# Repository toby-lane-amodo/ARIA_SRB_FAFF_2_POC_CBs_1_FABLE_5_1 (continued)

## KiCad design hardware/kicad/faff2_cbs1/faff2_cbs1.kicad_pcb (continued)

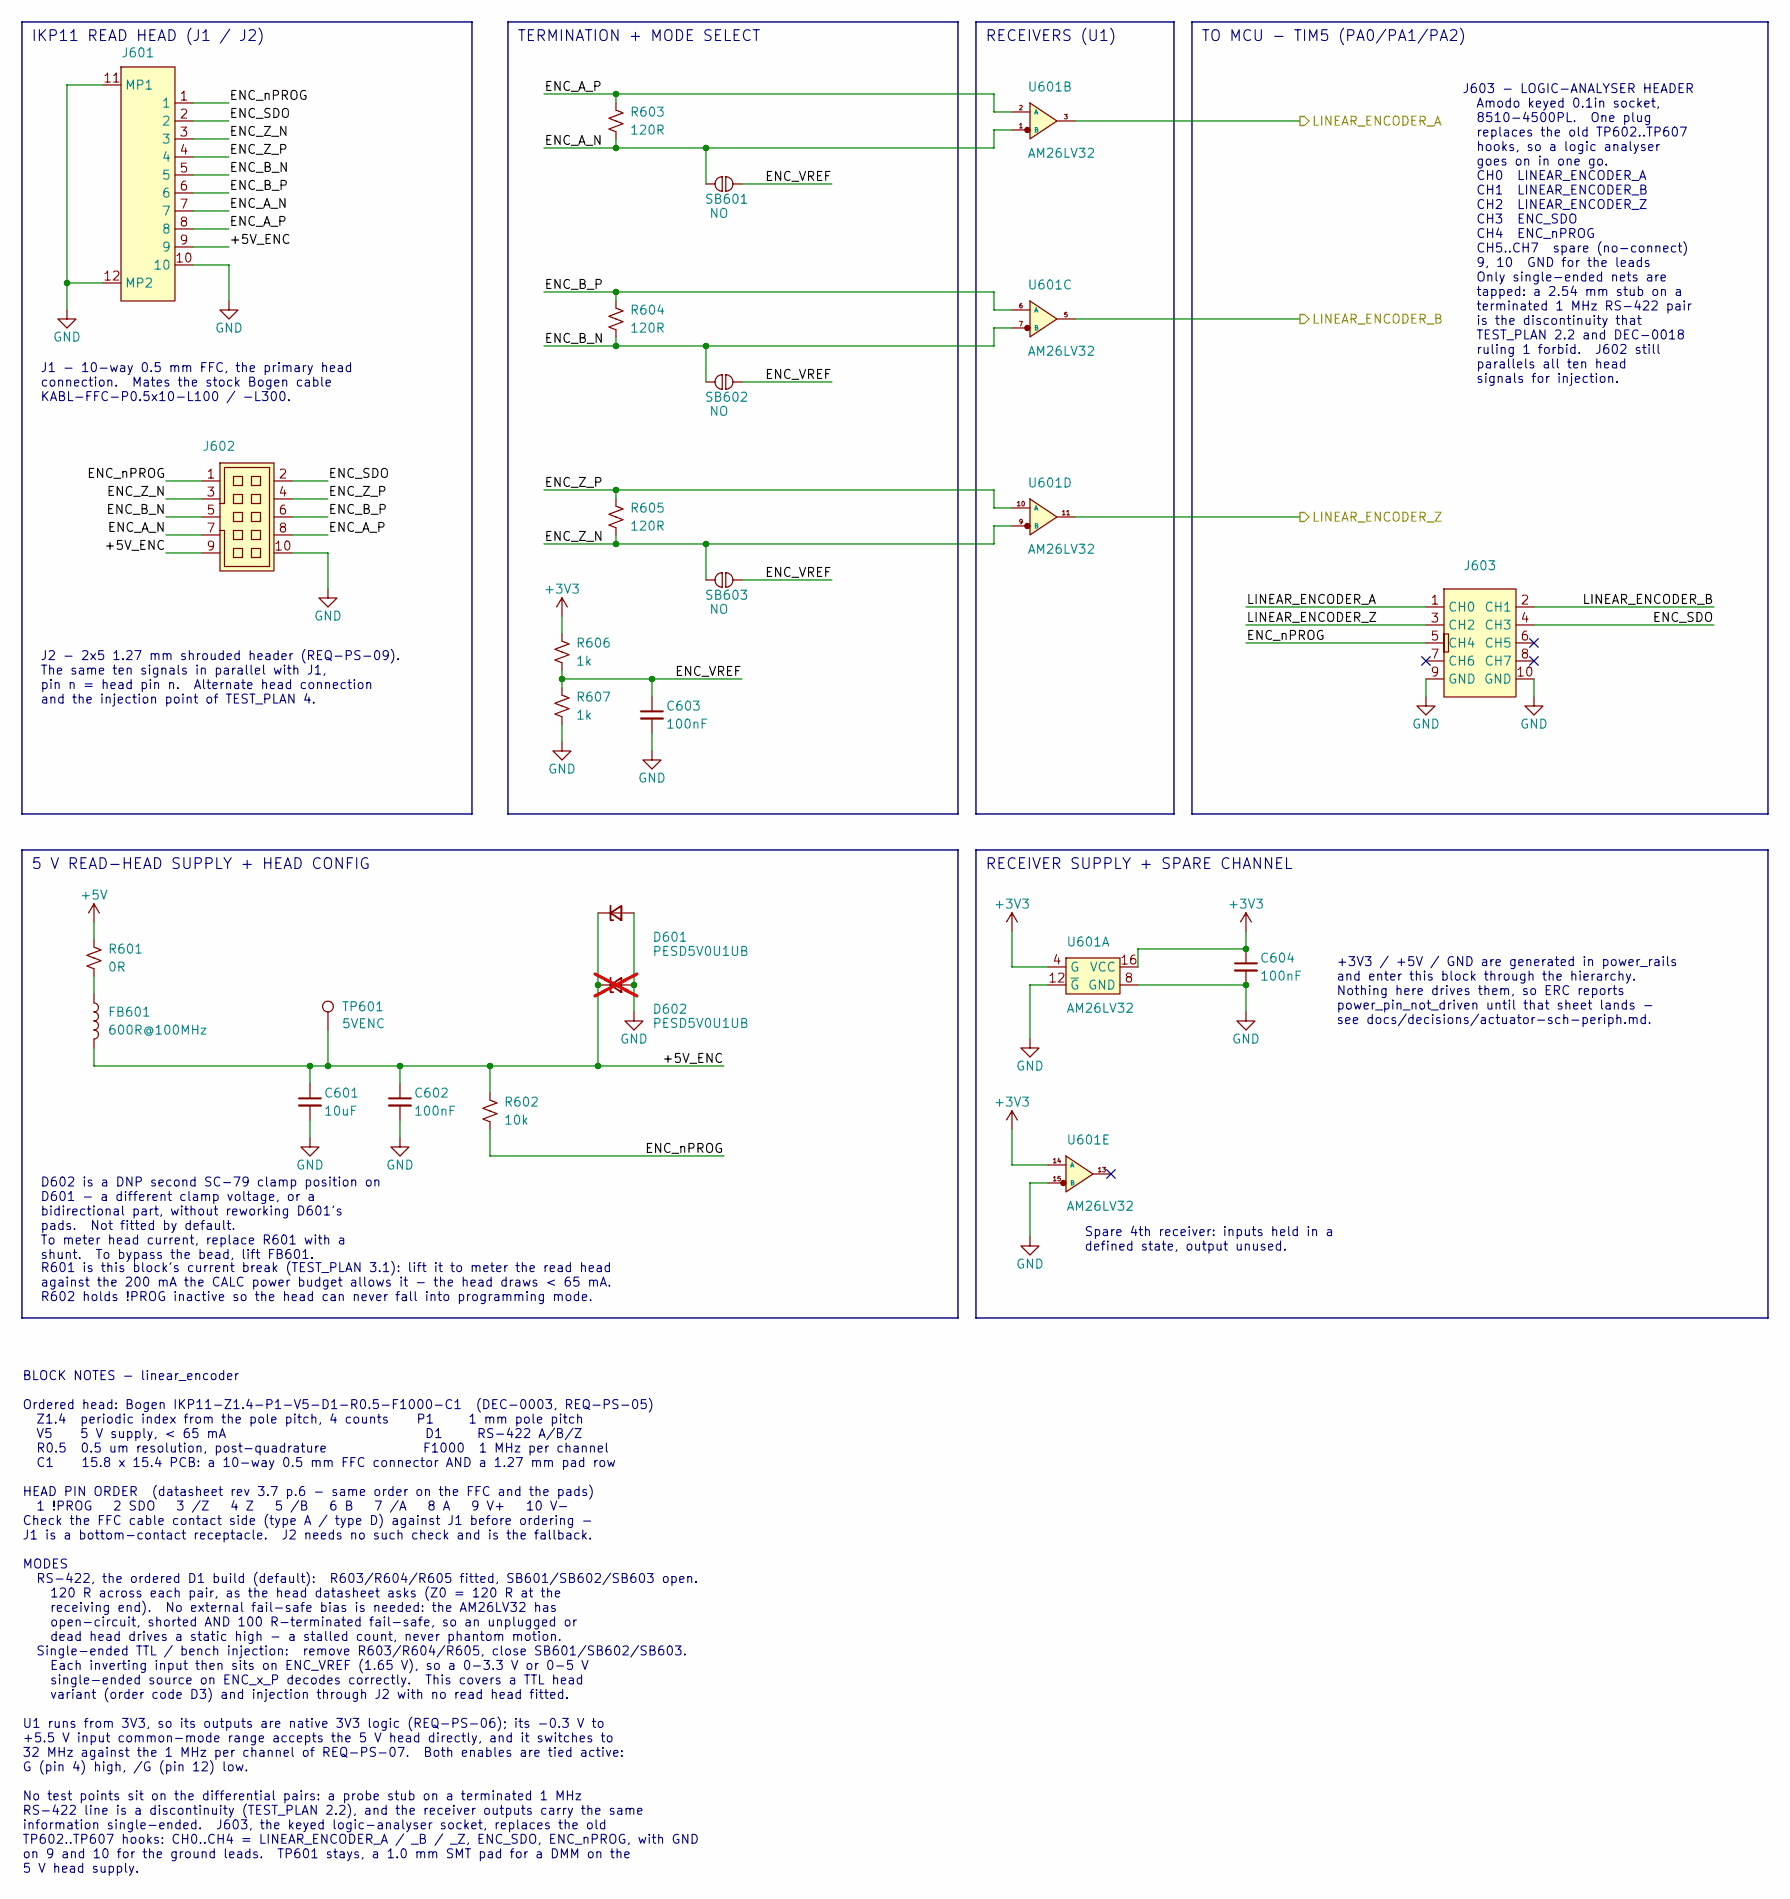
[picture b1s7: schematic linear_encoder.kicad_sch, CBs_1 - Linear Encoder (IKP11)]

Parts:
C601: 10uF; C_0805_2012Metric; mpn GRM21BR61E106MA73L
C602, C603, C604: 100nF; C_0603_1608Metric; mpn C0603C104M5RACAUTO
D601: PESD5V0U1UB; SC-79 (SOD523); mpn PESD5V0U1UB\,115
D602: PESD5V0U1UB; SC-79 (SOD523); mpn PESD5V0U1UB\,115; not fitted
FB601: 600R@100MHz; R_0603_1608Metric; mpn BLM18HE601SN1D
J601: FH12-10S-0.5SH(55); mpn FH12-10S-0.5SH(55); jlcpn C506791
J602: FTSH-105-01-L-DV-K-TR; mpn FTSH-105-01-L-DV-K-TR
J603: 8510-4500PL; 8510-4500PL_LOGIC_TEST; mpn 8510-4500PL
R601: 0R; R_0603_1608Metric; mpn RC0603FR-070RL
R602: 10k; R_0603_1608Metric; mpn ERJ-3EKF1002V
R603, R604, R605: 120R; R_0603_1608Metric; mpn ERJ-3EKF1200V
R606, R607: 1k; R_0603_1608Metric; mpn CR0603AFX-1001ELF
SB601, SB602, SB603: NO; SOLDER_JUMPER_NO
TP601: 5VENC; TestPoint_Pad_D1.0mm
U601: AM26LV32; SOIC-16-N; mpn AM26LV32CDR

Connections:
+3V3: C604.1, R606.1, U601.4 (G), U601.14 (A), U601.16 (VCC); also elsewhere on the board
+5V: R601.1; also elsewhere on the board
/linear_encoder/+5V_ENC: C601.1, C602.1, D601.1 (K), D602.1 (K), FB601.2, J601.9, J602.9, R602.1, TP601.1
/linear_encoder/ENC_A_N: J601.7, J602.7, R603.2, SB601.1, U601.1 (B)
/linear_encoder/ENC_A_P: J601.8, J602.8, R603.1, U601.2 (A)
/linear_encoder/ENC_B_N: J601.5, J602.5, R604.2, SB602.1, U601.7 (B)
/linear_encoder/ENC_B_P: J601.6, J602.6, R604.1, U601.6 (A)
/linear_encoder/ENC_SDO: J601.2, J602.2, J603.4 (CH3)
/linear_encoder/ENC_VREF: C603.1, R606.2, R607.1, SB601.2, SB602.2, SB603.2
/linear_encoder/ENC_Z_N: J601.3, J602.3, R605.2, SB603.1, U601.9 (B)
/linear_encoder/ENC_Z_P: J601.4, J602.4, R605.1, U601.10 (A)
/linear_encoder/ENC_nPROG: J601.1, J602.1, J603.5 (CH4), R602.2
/linear_encoder/LINEAR_ENCODER_A: J603.1 (CH0), U601.3; also elsewhere on the board
/linear_encoder/LINEAR_ENCODER_B: J603.2 (CH1), U601.5; also elsewhere on the board
/linear_encoder/LINEAR_ENCODER_Z: J603.3 (CH2), U601.11; also elsewhere on the board
GND: C601.2, C602.2, C603.2, C604.2, D601.2 (A), D602.2 (A), J601.10, J601.11 (MP1), J601.12 (MP2), J602.10, J603.9 (GND), J603.10 (GND), R607.2, U601.8 (GND), U601.12 (~G), U601.15 (B); also elsewhere on the board
unnamed: FB601.1, R601.2

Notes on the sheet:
Spare 4th receiver: inputs held in a defined state, output unused.
TO MCU - TIM5 (PA0/PA1/PA2)
J1 - 10-way 0.5 mm FFC, the primary head connection. Mates the stock Bogen cable KABL-FFC-P0.5x10-L100 / -L300.
J603 - LOGIC-ANALYSER HEADER Amodo keyed 0.1in socket, 8510-4500PL. One plug replaces the old TP602..TP607 hooks, so a logic analyser goes on in one go. CH0 LINEAR_ENCODER_A CH1 LINEAR_ENCODER_B CH2 LINEAR_ENCODER_Z CH3 ENC_SDO CH4 ENC_nPROG CH5..CH7 spare (no-connect) 9, 10 GND for the leads Only 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
RECEIVERS (U1)
R601 is this block's current break (TEST_PLAN 3.1): lift it to meter the read head against the 200 mA the CALC power budget allows it - the head draws < 65 mA. R602 holds !PROG inactive so the head can never fall into programming mode.
TERMINATION + MODE SELECT
+3V3 / +5V / GND are generated in power_rails and enter this block through the hierarchy. Nothing here drives them, so ERC reports power_pin_not_driven until that sheet lands - see docs/decisions/actuator-sch-periph.md.
RECEIVER SUPPLY + SPARE CHANNEL
BLOCK NOTES - linear_encoder Ordered head: Bogen IKP11-Z1.4-P1-V5-D1-R0.5-F1000-C1 (DEC-0003, REQ-PS-05) Z1.4 periodic index from the pole pitch, 4 counts P1 1 mm pole pitch V5 5 V supply, < 65 mA D1 RS-422 A/B/Z R0.5 0.5 um resolution, post-quadrature F1000 1 MHz per channel C1 15.8 x 15.4 PCB: a 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
5 V READ-HEAD SUPPLY + HEAD CONFIG
D602 is a DNP second SC-79 clamp position on D601 - a different clamp voltage, or a bidirectional part, without reworking D601's pads. Not fitted by default. To meter head current, replace R601 with a shunt. To bypass the bead, lift FB601.
J2 - 2x5 1.27 mm shrouded header (REQ-PS-09). The same ten signals in parallel with J1, pin n = head pin n. Alternate head connection and the injection point of TEST_PLAN 4.
IKP11 READ HEAD (J1 / J2)

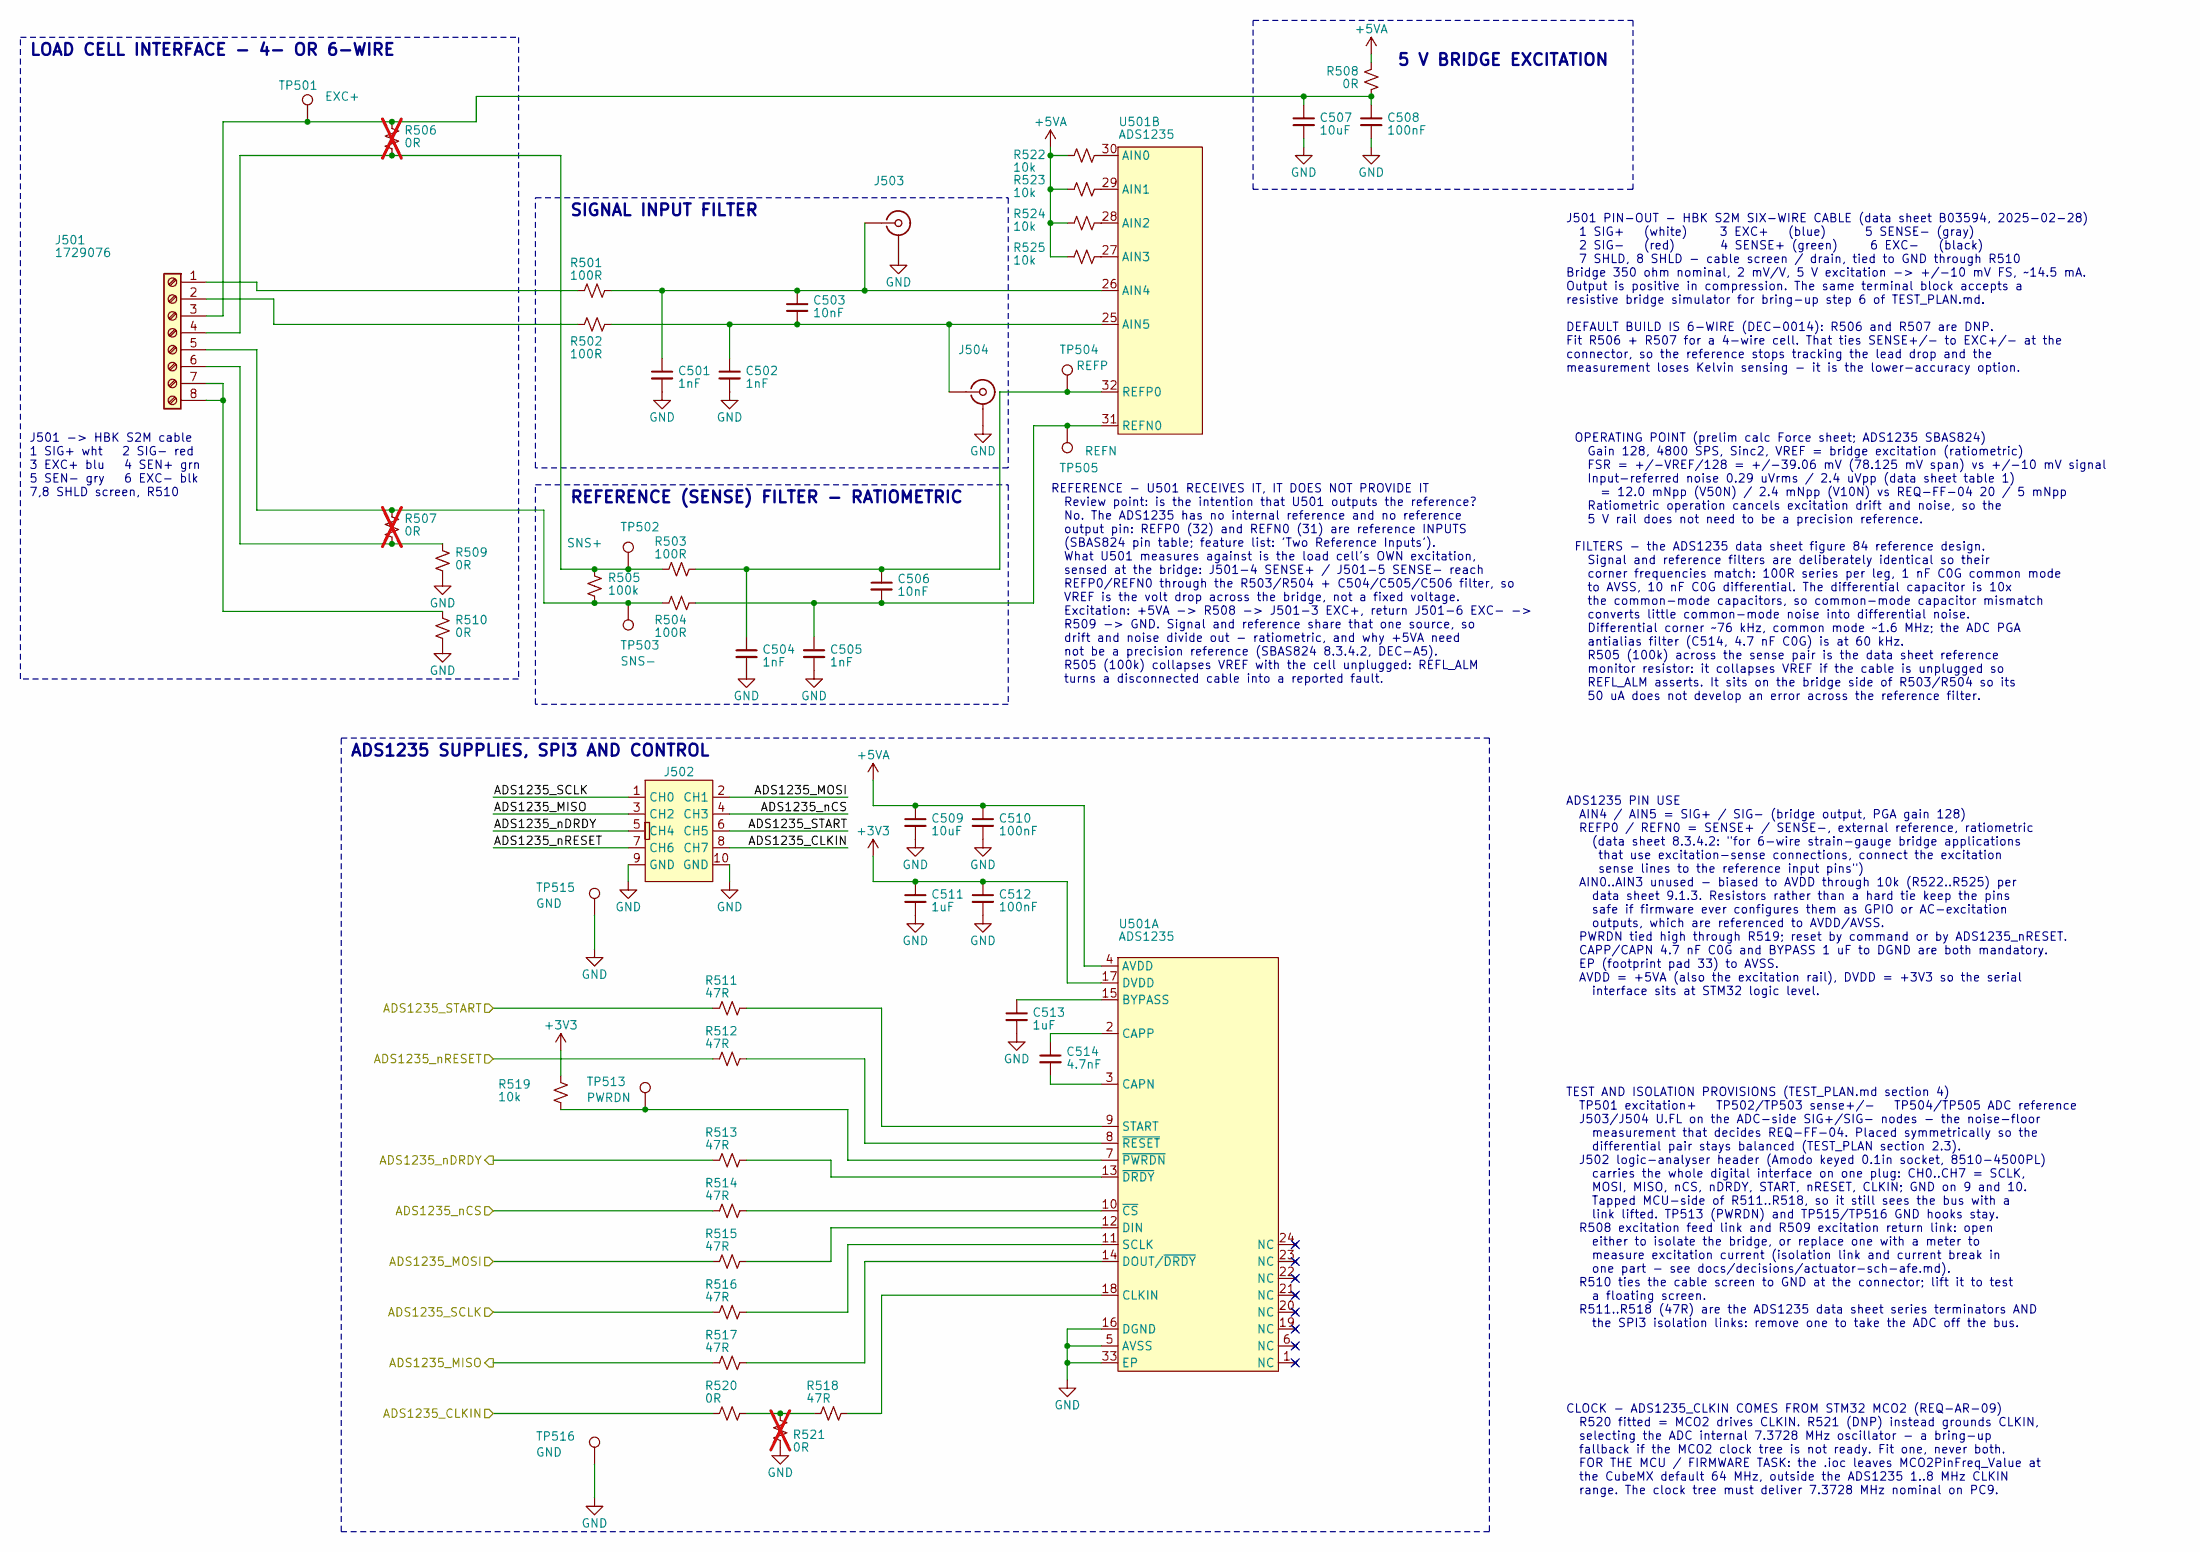
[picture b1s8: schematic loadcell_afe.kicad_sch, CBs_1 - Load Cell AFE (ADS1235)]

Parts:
C501, C502, C504, C505: 1nF; C_0603_1608Metric; mpn C0603C102F2GEC
C503, C506: 10nF; C_0603_1608Metric; mpn CGA3EAC0G2A103J080AC
C507, C509: 10uF; C_0805_2012Metric; mpn GRM21BR61E106MA73L
C508, C510, C512: 100nF; C_0402_1005Metric; mpn 04025C104KAT2A
C511, C513: 1uF; C_0603_1608Metric; mpn CL10B105KO8NNNC
C514: 4.7nF; C_0805_2012Metric; mpn C0805C472J2GEC7210
J501: 1729076; mpn 1729076
J502: 8510-4500PL; 8510-4500PL_LOGIC_TEST; mpn 8510-4500PL
J503, J504: CONUFL001-SMD; mpn CONUFL001-SMD-T
R501, R502, R503, R504: 100R; R_0603_1608Metric; mpn ERA3AEB101V
R505: 100k; R_0603_1608Metric; mpn ERJ-3EKF1003V
R506, R507, R521: 0R; R_0603_1608Metric; mpn RC0603FR-070RL; not fitted
R508, R509, R510, R520: 0R; R_0603_1608Metric; mpn RC0603FR-070RL
R511, R512, R513, R514, R515, R516, R517, R518: 47R; R_0603_1608Metric; mpn ERJ-3EKF47R0V
R519, R522, R523, R524, R525: 10k; R_0603_1608Metric; mpn ERJ-3EKF1002V
TP501: EXC+; KeystoneMiniatureTestLoop; mpn 5002
TP502: SNS+; TestPoint_Pad_D1.0mm
TP503: SNS-; TestPoint_Pad_D1.0mm
TP504: REFP; TestPoint_Pad_D1.0mm
TP505: REFN; TestPoint_Pad_D1.0mm
TP513: PWRDN; KeystoneMiniatureTestLoop; mpn 5002
TP515, TP516: GND; KeystoneMiniatureTestLoop; mpn 5002
U501: ADS1235; VQFN RHB 32 5x5 mm 0.5 pitch; mpn ADS1235IRHBT

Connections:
+3V3: C511.1, C512.1, R519.1, U501.17 (DVDD); also elsewhere on the board
+5VA: C509.1, C510.1, R508.1, R522.1, R523.1, R524.1, R525.1, U501.4 (AVDD); also elsewhere on the board
/loadcell_afe/ADS1235_CLKIN: J502.8 (CH7), R520.1; also elsewhere on the board
/loadcell_afe/ADS1235_MISO: J502.3 (CH2), R517.1; also elsewhere on the board
/loadcell_afe/ADS1235_MOSI: J502.2 (CH1), R515.1; also elsewhere on the board
/loadcell_afe/ADS1235_SCLK: J502.1 (CH0), R516.1; also elsewhere on the board
/loadcell_afe/ADS1235_START: J502.6 (CH5), R511.1; also elsewhere on the board
/loadcell_afe/ADS1235_nCS: J502.4 (CH3), R514.1; also elsewhere on the board
/loadcell_afe/ADS1235_nDRDY: J502.5 (CH4), R513.1; also elsewhere on the board
/loadcell_afe/ADS1235_nRESET: J502.7 (CH6), R512.1; also elsewhere on the board
GND: C501.2, C502.2, C504.2, C505.2, C507.2, C508.2, C509.2, C510.2, C511.2, C512.2, C513.2, J502.9 (GND), J502.10 (GND), J503.2 (Ext), J503.3 (Ext), J504.2 (Ext), J504.3 (Ext), R509.2, R510.2, R521.2, TP515.1, TP516.1, U501.5 (AVSS), U501.16 (DGND), U501.33 (EP); also elsewhere on the board
unnamed: C507.1, C508.1, J501.3, R506.1, R508.2, TP501.1
unnamed: J501.1, R501.1
unnamed: J501.2, R502.1
unnamed: J501.4, R503.1, R505.1, R506.2, TP502.1
unnamed: J501.5, R504.1, R505.2, R507.1, TP503.1
unnamed: J501.6, R507.2, R509.1
unnamed: J501.7, J501.8, R510.1
unnamed: C501.1, C503.1, J503.1 (In), R501.2, U501.26 (AIN4)
unnamed: C502.1, C503.2, J504.1 (In), R502.2, U501.25 (AIN5)
unnamed: R518.1, R520.2, R521.1
unnamed: C513.1, U501.15 (BYPASS)
unnamed: C514.2, U501.3 (CAPN)
unnamed: C514.1, U501.2 (CAPP)
unnamed: R518.2, U501.18 (CLKIN)
unnamed: R515.2, U501.12 (DIN)
unnamed: R517.2, U501.14 (DOUT/~DRDY)
unnamed: R516.2, U501.11 (SCLK)
unnamed: R511.2, U501.9 (START)
unnamed: R514.2, U501.10 (~CS)
unnamed: R513.2, U501.13 (~DRDY)
unnamed: R519.2, TP513.1, U501.7 (~PWRDN)
unnamed: R512.2, U501.8 (~RESET)
unnamed: R522.2, U501.30 (AIN0)
unnamed: R523.2, U501.29 (AIN1)
unnamed: R524.2, U501.28 (AIN2)
unnamed: R525.2, U501.27 (AIN3)
unnamed: C505.1, C506.2, R504.2, TP505.1, U501.31 (REFN0)
unnamed: C504.1, C506.1, R503.2, TP504.1, U501.32 (REFP0)

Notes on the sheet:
CLOCK - ADS1235_CLKIN COMES FROM STM32 MCO2 (REQ-AR-09) R520 fitted = MCO2 drives CLKIN. R521 (DNP) instead grounds CLKIN, selecting the ADC internal 7.3728 MHz oscillator - a bring-up fallback if the MCO2 clock tree is not ready. Fit one, never both. FOR THE MCU / FIRMWARE TASK: the .ioc leaves MC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
REFERENCE - U501 RECEIVES IT, IT DOES NOT PROVIDE IT Review point: is the intention that U501 outputs the reference? No. The ADS1235 has no internal reference and no reference output pin: REFP0 (32) and REFN0 (31) are reference INPUTS (SBAS824 pin table; feature list: 'Two Reference Inputs'). What 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
LOAD CELL INTERFACE - 4- OR 6-WIRE
OPERATING POINT (prelim calc Force sheet; ADS1235 SBAS824) Gain 128, 4800 SPS, Sinc2, VREF = bridge excitation (ratiometric) FSR = +/-VREF/128 = +/-39.06 mV (78.125 mV span) vs +/-10 mV signal Input-referred noise 0.29 uVrms / 2.4 uVpp (data sheet table 1) = 12.0 mNpp (V50N) / 2.4 mNpp (V10N) vs RE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
J501 -> HBK S2M cable 1 SIG+ wht 2 SIG- red 3 EXC+ blu 4 SEN+ grn 5 SEN- gry 6 EXC- blk 7,8 SHLD screen, R510
SIGNAL INPUT FILTER
ADS1235 SUPPLIES, SPI3 AND CONTROL
REFERENCE (SENSE) FILTER - RATIOMETRIC
ADS1235 PIN USE AIN4 / AIN5 = SIG+ / SIG- (bridge output, PGA gain 128) REFP0 / REFN0 = SENSE+ / SENSE-, external reference, ratiometric (data sheet 8.3.4.2: "for 6-wire strain-gauge bridge applications that use excitation-sense connections, connect the excitation sense lines to the reference input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
J501 PIN-OUT - HBK S2M SIX-WIRE CABLE (data sheet B03594, 2025-02-28) 1 SIG+ (white) 3 EXC+ (blue) 5 SENSE- (gray) 2 SIG- (red) 4 SENSE+ (green) 6 EXC- (black) 7 SHLD, 8 SHLD - cable screen / drain, tied to GND through R510 Bridge 350 ohm nominal, 2 mV/V, 5 V excitation -> +/-10 mV FS, ~14.5 mA. Ou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
TEST AND ISOLATION PROVISIONS (TEST_PLAN.md section 4) TP501 excitation+ TP502/TP503 sense+/- TP504/TP505 ADC reference J503/J504 U.FL on the ADC-side SIG+/SIG- nodes - the noise-floor measurement that decides REQ-FF-04. Placed symmetrically so the differential pair stays balanced (TEST_PLAN sectio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
5 V BRIDGE EXCITATION

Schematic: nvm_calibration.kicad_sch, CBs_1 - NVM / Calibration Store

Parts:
C801: 100nF; C_0603_1608Metric; mpn C0603C104M5RACAUTO
R801, R802: 0R; R_0603_1608Metric; mpn RC0603FR-070RL
R803, R804: 4.7k; R_0603_1608Metric; mpn ERJ-3EKF4701V
R805: 10k; R_0603_1608Metric; mpn ERJ-3EKF1002V
SB801, SB802: NC; SOLDER_JUMPER_NC
SB803: NO; SOLDER_JUMPER_NO
TP801: SCL; KeystoneMiniatureTestLoop; mpn 5002
TP802: SDA; KeystoneMiniatureTestLoop; mpn 5002
TP803: WP; TestPoint_Pad_D1.0mm
TP804, TP805: GND; KeystoneMiniatureTestLoop; mpn 5002
U801: 24FC16T-I/OT; SOT23-5 - TI; mpn 24FC16T-I/OT

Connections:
+3V3: C801.1, R801.1, R802.1, SB803.2, U801.4 (VCC); also elsewhere on the board
/mcu/EEPROM_SCL: R803.2, SB801.1, TP801.1; also elsewhere on the board
/mcu/EEPROM_SDA: R804.2, SB802.1, TP802.1; also elsewhere on the board
GND: C801.2, R805.2, TP804.1, TP805.1, U801.2 (VSS); also elsewhere on the board
unnamed: R801.2, R803.1
unnamed: R802.2, R804.1
unnamed: SB801.2, U801.1 (SCL)
unnamed: SB802.2, U801.3 (SDA)
unnamed: R805.1, SB803.1, TP803.1, U801.5 (WP)

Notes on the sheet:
R801/R802 are the removable links of TEST_PLAN 4: lift either to drop its pull-up. SB801/SB802 are cut to take the EEPROM off I2C1 while the bus stays pulled up - this block owns that break, so mcu must not duplicate it. The SDA pull-up crosses the SCL run, no junction.
BLOCK NOTES - nvm_calibration U1 = Microchip 24FC16T-I/OT, 16 kbit (2048 x 8) I2C EEPROM in SOT-23-5. Pin map verified against the datasheet package drawing (DS20001703R p.1): 1 SCL 2 VSS 3 SDA 4 VCC 5 WP. 1.7-5.5 V and 1 MHz capable, so it keeps up with I2C1 at either 400 kHz or Fast-mode Plus, an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
I2C1 BUS, PULL-UPS, ISOLATION
GND hooks beside TP801/TP802 for the scope or analyser clips.
EEPROM, DECOUPLING, WRITE PROTECT
GROUND HOOKS
+3V3 and GND are generated in power_rails and enter this block through the hierarchy; nothing here drives them, so ERC reports power_pin_not_driven until that sheet lands. See docs/decisions/actuator-sch-periph.md.
WP is ACTIVE HIGH. R805 holds it low, so the part is writable and firmware can store calibration at any time; solder SB803 to lock the device permanently. TP3 lets a jig drive WP either way. This resolves OQ-06 - no MCU pin is spent on write protect.

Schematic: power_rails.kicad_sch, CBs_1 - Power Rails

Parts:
C301, C302, C315, C316: 10uF; C_1206_3216Metric; Voltage 50V; mpn GRT31CR61H106ME01L
C303, C317: 220nF; C_0805_2012Metric; mpn HMK212B7224KG-T
C304, C318: 1uF; C_0603_1608Metric; mpn CL10B105KO8NNNC
C305, C308, C311, C314, C319, C322, C324: 100nF; C_0603_1608Metric; mpn C0603C104M5RACAUTO
C306, C307, C320, C321: 22uF; C_1206_3216Metric; Voltage 16V; mpn CL31A226MOCLNNC
C309, C312: 10uF; C_0603_1608Metric; mpn CL10B105KO8NNNC
C310, C313, C323: 10uF; C_0603_1608Metric; mpn ZRB18AR61A106ME01L
D303: SM0805URC; LED 0805 SM0805; mpn SM0805URC
FB301: 600R@100MHz; R_0603_1608Metric; mpn BLM18HE601SN1D
J301: PH1-06-UA; Adam_Tech_PH1-06-UA; mpn PH1-06-UA
L301: 15uH; L_Bourns_SRR1210; mpn SRR1210-150M
L302: 6.8uH; IND_ASPI-0630HI; mpn ASPI-0630HI-6R8M
R301, R308, R313: 100k; R_0603_1608Metric; mpn ERJ-3EKF1003V
R302, R309: 8.2k; R_0603_1608Metric; mpn ERJ-3EKF8201V
R303: 64k9; R_0603_1608Metric; tolerance 0.1%; mpn ERA-3AEB6492V
R304: 12k7; R_0603_1608Metric; Tolerance 0.1%; mpn ERA-3AEB1272V
R305, R306, R307, R312: 0R; R_0603_1608Metric; mpn RC0603FR-070RL
R310: 100k; R_0603_1608Metric; tolerance 0.1%; mpn ERA-3VEB1003V
R311: 43k; R_0603_1608Metric; mpn CRCW060343K0FKEA
R314: 330R; R_0603_1608Metric; mpn ERJ-3EKF3300V
R315, R316, R317, R318: 1k; R_0603_1608Metric; mpn CR0603AFX-1001ELF
TP302: +6V0; TestPoint_Dual_D1.5mm_H1.0mm
TP303: +5V; TestPoint_Dual_D1.5mm_H1.0mm
TP304: +5VA; TestPoint_Dual_D1.5mm_H1.0mm
TP306: +3V3; TestPoint_Dual_D1.5mm_H1.0mm
TP307: +3V3A; TestPoint_Dual_D1.5mm_H1.0mm
TP308: PGOOD; KeystoneMiniatureTestLoop; mpn 5002
TP309, TP310, TP311, TP312: GND; KeystoneMiniatureTestLoop; mpn 5002
U301, U304: LMR33630; PowerPAD SOIC-8 HSOIC (8); mpn LMR33630
U302, U303: ADPL42005; LFCSP-8 - 3x3mm body - 0.5mm pitch - 2.5x1.8mm EP; mpn ADPL42005ACPZ-5.0-R7

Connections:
+3V3: FB301.1, J301.2, R312.2, R313.1, R314.1, TP306.1; also elsewhere on the board
+3V3A: C323.1, C324.1, FB301.2, J301.3, TP307.1; also elsewhere on the board
+5V: J301.1, R306.2, TP303.1; also elsewhere on the board
+5VA: R307.2, TP304.1; also elsewhere on the board
/power_entry_24v/V24_LOGIC: C301.1, C302.1, C303.1, C315.1, C316.1, C317.1, R301.1, R308.1, U301.2 (VIN), U304.2 (VIN); also elsewhere on the board
/power_rails/+6V0: C309.1, C312.1, R305.2, TP302.1, U302.5 (EN), U302.8 (VIN), U303.5 (EN), U303.8 (VIN)
/power_rails/RAIL_PGOOD: D303.2, R313.2, R315.2, R316.2, R317.2, R318.2, TP308.1
GND: C301.2, C302.2, C303.2, C304.2, C306.2, C307.2, C308.2, C309.2, C310.2, C311.2, C312.2, C313.2, C314.2, C315.2, C316.2, C317.2, C318.2, C320.2, C321.2, C322.2, C323.2, C324.2, J301.4, J301.5, J301.6, R302.2, R304.2, R309.2, R311.2, TP302.2, TP303.2, TP304.2, TP306.2, TP307.2, TP309.1, TP310.1, TP311.1, TP312.1, U301.1 (PGND), U301.TP (GND), U302.3 (GND), U302.6 (GND), U302.9 (EP), U303.3 (GND), U303.6 (GND), U303.9 (EP), U304.1 (PGND), U304.TP (GND); also elsewhere on the board
unnamed: C306.1, C307.1, C308.1, L301.2, R303.1, R305.1
unnamed: C320.1, C321.1, C322.1, L302.2, R310.1, R312.1
unnamed: D303.1, R314.2
unnamed: C305.1, U301.7 (BOOT)
unnamed: R301.2, R302.1, U301.3 (EN)
unnamed: R303.2, R304.1, U301.5 (FB)
unnamed: R315.1, U301.4 (PG)
unnamed: C305.2, L301.1, U301.8 (SW)
unnamed: C304.1, U301.6 (VCC)
unnamed: R317.1, U302.7 (PG)
unnamed: C310.1, C311.1, R306.1, U302.1 (VOUT), U302.2 (SENSE)
unnamed: R318.1, U303.7 (PG)
unnamed: C313.1, C314.1, R307.1, U303.1 (VOUT), U303.2 (SENSE)
unnamed: C319.1, U304.7 (BOOT)
unnamed: R308.2, R309.1, U304.3 (EN)
unnamed: R310.2, R311.1, U304.5 (FB)
unnamed: R316.1, U304.4 (PG)
unnamed: C319.2, L302.1, U304.8 (SW)
unnamed: C318.1, U304.6 (VCC)

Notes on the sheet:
6.0 V, not 5.0 V: it is the ADPL42005's own characterised VIN = VOUT + 1 V point, so the LDOs meet their noise and PSRR numbers on +5VA, which carries REQ-FF-04. R303/R304 are sized so the worst-case floor clears 6.0 V, not just the nominal: 6.009 / 6.110 / 6.212 V. Was 5.5 V while the TPS7A20's 6.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
D. ANALOG 3V3, RAIL POWER-GOOD, AND THE RAIL PROBE HEADER
POWER SOURCE DECLARATIONS One PWR_FLAG per rail produced here, at the regulator that makes it, on the load side of that rail's 0R link. No other sheet may add one for these nets.
RAIL PROBE HEADER (TEST_PLAN 4) One header to check every logic rail with a DMM during bring-up steps 2 and 3 of TEST_PLAN 5. It only observes: the rails, their isolation links and their current breaks are the rest of this sheet. 1 +5V 2 +3V3 3 +3V3A 4 GND 5 GND 6 GND +24V IS DELIBERATELY NOT ON TH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
A. PRE-REGULATOR V24_LOGIC -> 6.0 V (LMR33630, 400 kHz)
EN is tied to each LDO input - the datasheet's own automatic-startup connection - so the 5 V rails follow the pre-regulator with no sequencing logic. SENSE ties to VOUT at the regulator, not past the 0R link, so lifting the link cannot open the loop. PG is unused: no-connect, not tied to RAIL_PGOOD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
C. 3V3 REGULATOR V24_LOGIC -> 3.3 V (LMR33630, 400 kHz)
BLOCK: power_rails - rail set and topology; answers OQ-02 and OQ-07 RAILS +6V0 LMR33630 buck from V24_LOGIC. Pre-regulator only, local to this sheet. +5V ADPL42005 LDO from +6V0. IKP11 read head (<65 mA plus RS-422 drive) and spare. +5VA ADPL42005 LDO from +6V0. ADS1235 / ADS1120 AVDD and the AFE 5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
PER RAIL (docs/TEST_PLAN.md 3.1) one 0R link that is BOTH the isolation link and the current-measurement break, a test point downstream of it, on a dual pad so a scope ground clips beside the probe. No test point sits on a feedback node: R305 +6V0, R306 +5V, R307 +5VA, R312 +3V3, FB301 +3V3A. Per-C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
B. POST-REGULATED 5 V RAILS (ADPL42005: +5V digital, +5VA analog)
FB301 is the +3V3A isolation link and current break: lift it and the ADC digital supplies are cut loose.

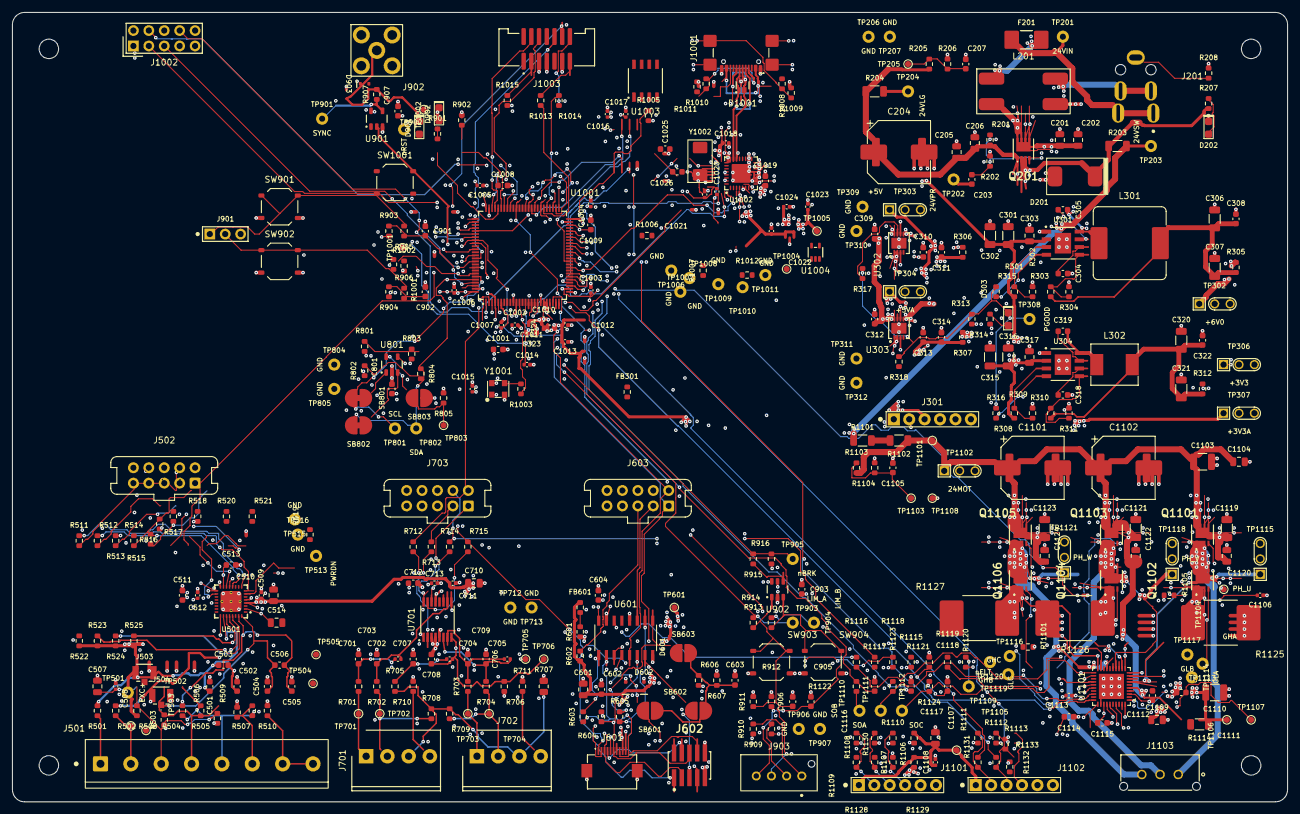
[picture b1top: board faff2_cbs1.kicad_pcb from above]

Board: 6 copper layers, 210.0 x 130.0 mm, 412 parts (0 on the bottom side), 240 nets.

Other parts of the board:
H1, H2, H3, H4: MountingHole_3.2mm_M3_NO-PAD_NPTH

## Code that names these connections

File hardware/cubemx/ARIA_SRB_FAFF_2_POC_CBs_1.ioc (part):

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Mcu.Name=STM32H723VETx
Mcu.Package=LQFP100
Mcu.UserName=STM32H723VETx
PA0.GPIOParameters=GPIO_Label
PA0.GPIO_Label=LINEAR_ENCODER_A
PA0.Signal=S_TIM5_CH1
PA1.GPIOParameters=GPIO_Label
PA1.GPIO_Label=LINEAR_ENCODER_B
PA1.Signal=S_TIM5_CH2
PA11.GPIOParameters=GPIO_Label
PA11.GPIO_Label=LED_2
PA11.Signal=GPIO_Output
PA12.GPIOParameters=GPIO_Label
PA12.GPIO_Label=LED_1
PA12.Signal=GPIO_Output
PA13(JTMS/SWDIO).Mode=Trace_Asynchronous_SW
PA13(JTMS/SWDIO).Signal=DEBUG_JTMS-SWDIO
PA14(JTCK/SWCLK).Mode=Trace_Asynchronous_SW
PA14(JTCK/SWCLK).Signal=DEBUG_JTCK-SWCLK
PA15(JTDI).GPIOParameters=GPIO_Label
PA15(JTDI).GPIO_Label=ADS1235_nCS
PA15(JTDI).Mode=NSS_Signal_Hard_Output
PA15(JTDI).Signal=SPI3_NSS
PA2.GPIOParameters=GPIO_Label
PA2.GPIO_Label=LINEAR_ENCODER_Z
PA2.Signal=S_TIM5_CH3
PA3.Mode=Device_HS
PA3.Signal=USB_OTG_HS_ULPI_D0
PA4.GPIOParameters=GPIO_Label
PA4.GPIO_Label=MOTOR_FETTEMP
PA4.Signal=ADCx_INP18
PA5.Mode=Device_HS
PA5.Signal=USB_OTG_HS_ULPI_CK
PA6.GPIOParameters=GPIO_Label
PA6.GPIO_Label=MOTOR_I_A
PA6.Signal=ADCx_INP3
PA7.GPIOParameters=GPIO_Label
PA7.GPIO_Label=MOTOR_I_C
PA7.Signal=ADCx_INP7
PA9.GPIOParameters=GPIO_Label
PA9.GPIO_Label=CONFIG_SPI_SCK
PA9.Mode=Full_Duplex_Master
PA9.Signal=SPI2_SCK
PB0.Mode=Device_HS
PB0.Signal=USB_OTG_HS_ULPI_D1
PB1.Mode=Device_HS
PB1.Signal=USB_OTG_HS_ULPI_D2
PB10.Mode=Device_HS
PB10.Signal=USB_OTG_HS_ULPI_D3
PB11.Mode=Device_HS
PB11.Signal=USB_OTG_HS_ULPI_D4
PB12.Mode=Device_HS
PB12.Signal=USB_OTG_HS_ULPI_D5
PB13.Mode=Device_HS
PB13.Signal=USB_OTG_HS_ULPI_D6
PB14.GPIOParameters=GPIO_Label
PB14.GPIO_Label=CONFIG_SPI_MISO
PB14.Mode=Full_Duplex_Master
PB14.Signal=SPI2_MISO
PB15.GPIOParameters=GPIO_Label
PB15.GPIO_Label=CONFIG_SPI_MOSI
PB15.Mode=Full_Duplex_Master
PB15.Signal=SPI2_MOSI
PB2.GPIOParameters=GPIO_Label
PB2.GPIO_Label=QSPI_P1_CLK
PB2.Mode=O1_P1_CLK
PB2.Signal=OCTOSPIM_P1_CLK
PB3(JTDO/TRACESWO).Mode=Trace_Asynchronous_SW
PB3(JTDO/TRACESWO).Signal=DEBUG_JTDO-SWO
PB5.Mode=Device_HS
PB5.Signal=USB_OTG_HS_ULPI_D7
PB6.GPIOParameters=GPIO_Label
PB6.GPIO_Label=QSPI_P1_nCS
PB6.Mode=OCTOSPI1_Port1_NCS
PB6.Signal=OCTOSPIM_P1_NCS
PB8.GPIOParameters=GPIO_Label
PB8.GPIO_Label=EEPROM_SCL
PB8.Mode=I2C
PB8.Signal=I2C1_SCL
PB9.GPIOParameters=GPIO_Label
PB9.GPIO_Label=EEPROM_SDA
PB9.Mode=I2C
PB9.Signal=I2C1_SDA
PC0.Mode=Device_HS
PC0.Signal=USB_OTG_HS_ULPI_STP
PC1.GPIOParameters=GPIO_Label
PC1.GPIO_Label=V24_MON
PC1.Signal=ADCx_INP11
PC10.GPIOParameters=GPIO_Label
PC10.GPIO_Label=ADS1235_SCLK
PC10.Mode=Full_Duplex_Master
PC10.Signal=SPI3_SCK
PC11.GPIOParameters=GPIO_Label
PC11.GPIO_Label=ADS1235_MISO
PC11.Mode=Full_Duplex_Master
PC11.Signal=SPI3_MISO
PC12.GPIOParameters=GPIO_Label
PC12.GPIO_Label=ADS1235_START
PC12.Signal=GPIO_Output
PC2_C.Mode=Device_HS
PC2_C.Signal=USB_OTG_HS_ULPI_DIR
PC3_C.Mode=Device_HS
PC3_C.Signal=USB_OTG_HS_ULPI_NXT
PC4.GPIOParameters=GPIO_Label
PC4.GPIO_Label=MOTOR_I_B
PC4.Signal=ADCx_INP4
PC5.GPIOParameters=GPIO_Label
PC5.GPIO_Label=VBUS_MON
PC5.Signal=ADCx_INP8
PC6.GPIOParameters=GPIO_Label
PC6.GPIO_Label=MOTOR_ENCODER_A
PC6.Signal=S_TIM3_CH1
PC7.GPIOParameters=GPIO_Label
PC7.GPIO_Label=MOTOR_ENCODER_B
PC7.Signal=S_TIM3_CH2
PC8.GPIOParameters=GPIO_Label
PC8.GPIO_Label=MOTOR_ENCODER_I
PC8.Signal=S_TIM3_CH3
PC9.GPIOParameters=GPIO_Label
PC9.GPIO_Label=ADS1235_CLKIN
PC9.Mode=Clock-out-2
PC9.Signal=RCC_MCO_2
PD0.GPIOParameters=GPIO_Label
PD0.GPIO_Label=ADS1235_nRESET
PD0.Signal=GPIO_Output
PD1.GPIOParameters=GPIO_Label
PD1.GPIO_Label=ADS1235_nDRDY
PD1.Signal=GPXTI1
PD10.GPIOParameters=GPIO_Label
PD10.GPIO_Label=DRV8323_EN
PD10.Signal=GPIO_Output
PD11.GPIOParameters=GPIO_Label
PD11.GPIO_Label=QSPI_P1_IO0
PD11.Mode=OCTOSPI1_IOL_Port1L
PD11.Signal=OCTOSPIM_P1_IO0
PD12.GPIOParameters=GPIO_Label
PD12.GPIO_Label=QSPI_P1_IO1
PD12.Mode=OCTOSPI1_IOL_Port1L
PD12.Signal=OCTOSPIM_P1_IO1
PD13.GPIOParameters=GPIO_Label
PD13.GPIO_Label=QSPI_P1_IO3
PD13.Mode=OCTOSPI1_IOL_Port1L
PD13.Signal=OCTOSPIM_P1_IO3
PD14.GPIOParameters=GPIO_Label
PD14.GPIO_Label=HALL2
PD14.Signal=GPIO_Input
PD15.GPIOParameters=GPIO_Label
PD15.GPIO_Label=HALL3
PD15.Signal=GPIO_Input
PD2.GPIOParameters=GPIO_Label
PD2.GPIO_Label=LIM_A
PD2.Signal=GPXTI2
PD3.GPIOParameters=GPIO_Label
PD3.GPIO_Label=ADS1120_nCS
PD3.Signal=GPIO_Output
PD4.GPIOParameters=GPIO_Label
PD4.GPIO_Label=LIM_B
PD4.Signal=GPXTI4
PD5.GPIOParameters=GPIO_Label
PD5.GPIO_Label=DRV8323_CAL
PD5.Signal=GPIO_Output
PD6.GPIOParameters=GPIO_Label
PD6.GPIO_Label=ADS1235_MOSI
PD6.Mode=Full_Duplex_Master
PD6.Signal=SPI3_MOSI
PD7.GPIOParameters=GPIO_Label
PD7.GPIO_Label=DRV8323_nCS
PD7.Signal=GPIO_Output
PD8.GPIOParameters=GPIO_Label
PD8.GPIO_Label=DBG_TX
PD8.Mode=Asynchronous
PD8.Signal=USART3_TX
PD9.GPIOParameters=GPIO_Label
PD9.GPIO_Label=DBG_RX
PD9.Mode=Asynchronous
PD9.Signal=USART3_RX
PE0.GPIOParameters=GPIO_Label
PE0.GPIO_Label=BTN_1
PE0.Signal=GPIO_Input
PE1.GPIOParameters=GPIO_Label
PE1.GPIO_Label=BTN_2
PE1.Signal=GPIO_Input
PE10.GPIOParameters=GPIO_Label
PE10.GPIO_Label=MOTOR_PWM_BL
PE10.Mode=PWM Generation2 CH2 CH2N
PE10.Signal=TIM1_CH2N
PE11.GPIOParameters=GPIO_Label
PE11.GPIO_Label=MOTOR_PWM_BH
PE11.Signal=S_TIM1_CH2
PE12.GPIOParameters=GPIO_Label
PE12.GPIO_Label=MOTOR_PWM_CL
PE12.Mode=PWM Generation3 CH3 CH3N
PE12.Signal=TIM1_CH3N
PE13.GPIOParameters=GPIO_Label
PE13.GPIO_Label=MOTOR_PWM_CH
PE13.Signal=S_TIM1_CH3
PE14.GPIOParameters=GPIO_Label
PE14.GPIO_Label=HALL1
PE14.Signal=GPIO_Input
PE15.GPIOParameters=GPIO_Label
PE15.GPIO_Label=DRV8323_nFAULT
PE15.Mode=Activate-Break-Input
PE15.Signal=TIM1_BKIN
PE2.GPIOParameters=GPIO_Label
PE2.GPIO_Label=QSPI_P1_IO2
PE2.Mode=OCTOSPI1_IOL_Port1L
PE2.Signal=OCTOSPIM_P1_IO2
PE4.GPIOParameters=GPIO_Label
PE4.GPIO_Label=USB3320_nRESET
PE4.Signal=GPIO_Output
PE5.GPIOParameters=GPIO_Label
PE5.GPIO_Label=SYNC_TRIG
PE5.Signal=S_TIM15_CH1
PE6.GPIOParameters=GPIO_Label
PE6.GPIO_Label=LIMIT_nBRK
PE6.Mode=Activate-Break-Input-2
PE6.Signal=TIM1_BKIN2
PE8.GPIOParameters=GPIO_Label
PE8.GPIO_Label=MOTOR_PWM_AL
PE8.Mode=PWM Generation1 CH1 CH1N
PE8.Signal=TIM1_CH1N
PE9.GPIOParameters=GPIO_Label
PE9.GPIO_Label=MOTOR_PWM_AH
PE9.Signal=S_TIM1_CH1
PH0-OSC_IN.Mode=HSE-External-Clock-Source
PH0-OSC_IN.Signal=RCC_OSC_IN
RCC.SYSCLKFreq_VALUE=64000000
board=custom
